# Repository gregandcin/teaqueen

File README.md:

# TeaQueen
An Alice Inspired Split Keyboard

## About the TeaQueen

The TeaQueen is a split, Alice keyboard running QMK firmware, with VIA and Vial compatibility (firmware to be realeased later). Based off of the [Red Queen](https://github.com/dbostian/redqueen) by [Dan Bostian](https://github.com/dbostian). 

V1 of the board, aka the Scuffed Edition, uses Kailh Hotswap sockets and Pro Micro compatitble dev boards, with a focus on [RP2040 Community Edition boards](https://docs.qmk.fm/#/platformdev_rp2040?id=rp2040_ce) such as the Elite-Pi.

## Why?

A PCB made by a factory is easier to assemble than handwiring.

## Want to make modifications?
This PCB uses the [Kiswitch](https://github.com/kiswitch/kiswitch) library as a globally installed pluggin in KiCad 7, so make sure to install that if you want to properly. Otherwise, everything is there for you as local libraries.

## Future Editions
A list of potential TODOs:

- [ ] Regular Solder socket boards
- [ ] An integrated RP2040 MCU
- [ ] A wireless edition

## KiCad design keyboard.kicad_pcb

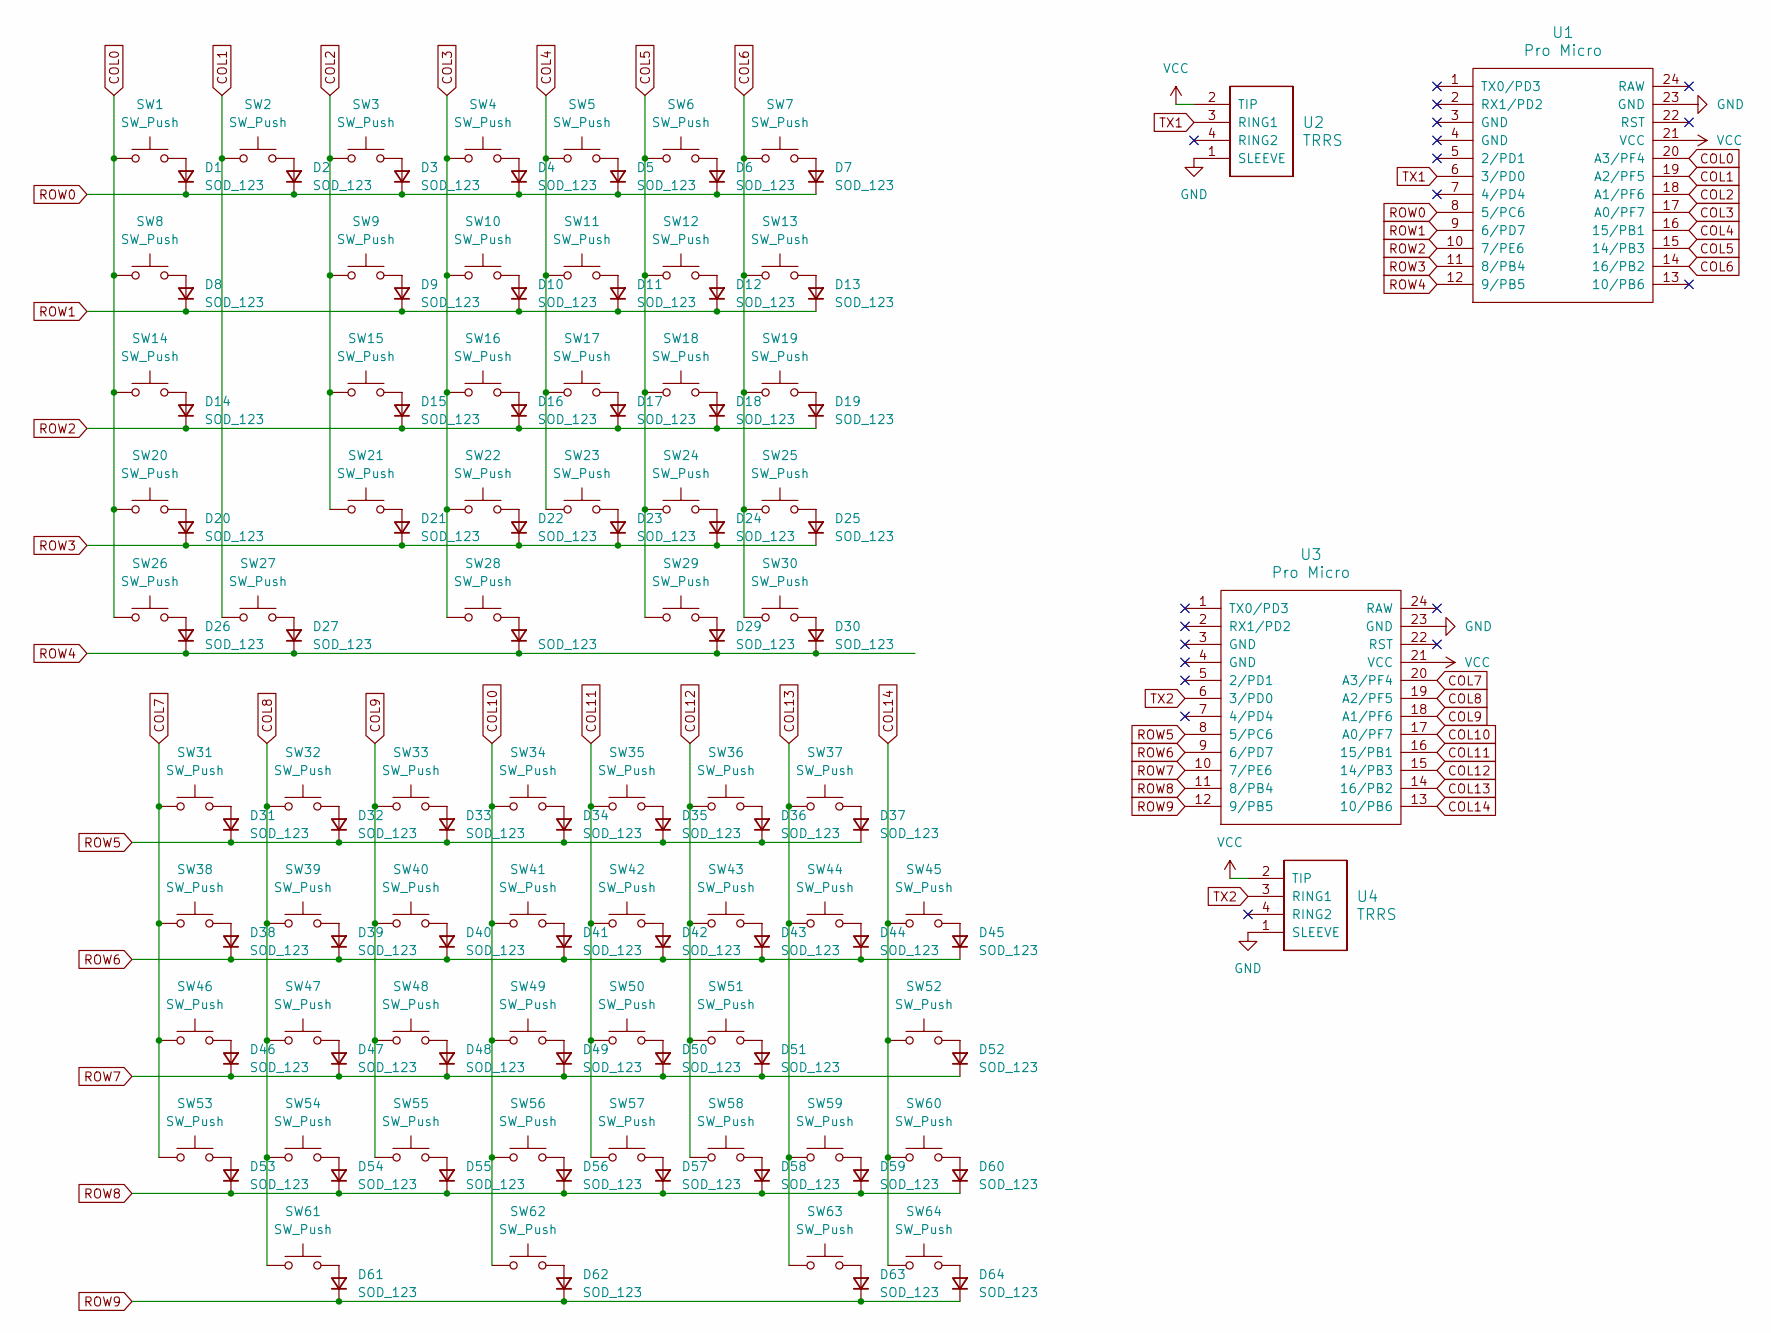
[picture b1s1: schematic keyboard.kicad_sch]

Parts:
D1, D2, D3, D4, D5, D6, D7, D8, D9, D10, D11, D12, D13, D14, D15, D16, D17, D18, D19, D20, D21, D22, D23, D24, D25, D26, D27, D28, D29, D30, D31, D32, D33, D34, D35, D36, D37, D38, D39, D40, D41, D42, D43, D44, D45, D46, D47, D48, D49, D50, D51, D52, D53, D54, D55, D56, D57, D58, D59, D60, D61, D62, D63, D64: SOD_123; D_SOD-123; MPN 1N914BWS; JLCPCB Part # C258181
SW1, SW2, SW3, SW4, SW5, SW6, SW7, SW9, SW10, SW11, SW12, SW13, SW15, SW16, SW17, SW18, SW19, SW21, SW22, SW23, SW24, SW25, SW27, SW30, SW31, SW32, SW33, SW34, SW35, SW36, SW38, SW39, SW40, SW41, SW42, SW43, SW44, SW46, SW47, SW48, SW49, SW50, SW51, SW53, SW54, SW55, SW56, SW57, SW58, SW60, SW63: SW_Push; SW_Hotswap_Kailh_MX_1.00u
SW8, SW26, SW28, SW45, SW62, SW64: SW_Push; SW_Hotswap_Kailh_MX_1.50u
SW14, SW59: SW_Push; SW_Hotswap_Kailh_MX_1.75u
SW20, SW52: SW_Push; SW_Hotswap_Kailh_MX_2.25u
SW29, SW37: SW_Push; SW_Hotswap_Kailh_MX_2.00u
SW61: SW_Push; SW_Hotswap_Kailh_MX_2.75u
U1, U3: Pro Micro; ArduinoProMicro
U2, U4: TRRS; TRRS-PJ-320A; MPN PJ-320A; JLCPCB Part # C2884926

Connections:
COL0: SW1.1, SW8.1, SW14.1, SW20.1, SW26.1, U1.20 (A3/PF4)
COL1: SW2.1, SW27.1, U1.19 (A2/PF5)
COL2: SW3.1, SW9.1, SW15.1, SW21.1, U1.18 (A1/PF6)
COL3: SW4.1, SW10.1, SW16.1, SW22.1, SW28.1, U1.17 (A0/PF7)
COL4: SW5.1, SW11.1, SW17.1, SW23.1, U1.16 (15/PB1)
COL5: SW6.1, SW12.1, SW18.1, SW24.1, SW29.1, U1.15 (14/PB3)
COL6: SW7.1, SW13.1, SW19.1, SW25.1, SW30.1, U1.14 (16/PB2)
COL7: SW31.1, SW38.1, SW46.1, SW53.1, U3.20 (A3/PF4)
COL8: SW32.1, SW39.1, SW47.1, SW54.1, SW61.1, U3.19 (A2/PF5)
COL9: SW33.1, SW40.1, SW48.1, SW55.1, U3.18 (A1/PF6)
COL10: SW34.1, SW41.1, SW49.1, SW56.1, SW62.1, U3.17 (A0/PF7)
COL11: SW35.1, SW42.1, SW50.1, SW57.1, U3.16 (15/PB1)
COL12: SW36.1, SW43.1, SW51.1, SW58.1, U3.15 (14/PB3)
COL13: SW37.1, SW44.1, SW59.1, SW63.1, U3.14 (16/PB2)
COL14: SW45.1, SW52.1, SW60.1, SW64.1, U3.13 (10/PB6)
GND: U1.23 (GND), U2.1 (SLEEVE), U3.23 (GND), U4.1 (SLEEVE)
unnamed: D1.2 (A), SW1.2
unnamed: D2.2 (A), SW2.2
unnamed: D3.2 (A), SW3.2
unnamed: D4.2 (A), SW4.2
unnamed: D5.2 (A), SW5.2
unnamed: D6.2 (A), SW6.2
unnamed: D7.2 (A), SW7.2
unnamed: D8.2 (A), SW8.2
unnamed: D9.2 (A), SW9.2
unnamed: D10.2 (A), SW10.2
unnamed: D11.2 (A), SW11.2
unnamed: D12.2 (A), SW12.2
unnamed: D13.2 (A), SW13.2
unnamed: D14.2 (A), SW14.2
unnamed: D15.2 (A), SW15.2
unnamed: D16.2 (A), SW16.2
unnamed: D17.2 (A), SW17.2
unnamed: D18.2 (A), SW18.2
unnamed: D19.2 (A), SW19.2
unnamed: D20.2 (A), SW20.2
unnamed: D21.2 (A), SW21.2
unnamed: D22.2 (A), SW22.2
unnamed: D23.2 (A), SW23.2
unnamed: D24.2 (A), SW24.2
unnamed: D25.2 (A), SW25.2
unnamed: D26.2 (A), SW26.2
unnamed: D27.2 (A), SW27.2
unnamed: D28.2 (A), SW28.2
unnamed: D29.2 (A), SW29.2
unnamed: D30.2 (A), SW30.2
unnamed: D31.2 (A), SW31.2
unnamed: D32.2 (A), SW32.2
unnamed: D33.2 (A), SW33.2
unnamed: D34.2 (A), SW34.2
unnamed: D35.2 (A), SW35.2
unnamed: D36.2 (A), SW36.2
unnamed: D37.2 (A), SW37.2
unnamed: D38.2 (A), SW38.2
unnamed: D39.2 (A), SW39.2
unnamed: D40.2 (A), SW40.2
unnamed: D41.2 (A), SW41.2
unnamed: D42.2 (A), SW42.2
unnamed: D43.2 (A), SW43.2
unnamed: D44.2 (A), SW44.2
unnamed: D45.2 (A), SW45.2
unnamed: D46.2 (A), SW46.2
unnamed: D47.2 (A), SW47.2
unnamed: D48.2 (A), SW48.2
unnamed: D49.2 (A), SW49.2
unnamed: D50.2 (A), SW50.2
unnamed: D51.2 (A), SW51.2
unnamed: D52.2 (A), SW52.2
unnamed: D53.2 (A), SW53.2
unnamed: D54.2 (A), SW54.2
unnamed: D55.2 (A), SW55.2
unnamed: D56.2 (A), SW56.2
unnamed: D57.2 (A), SW57.2
unnamed: D58.2 (A), SW58.2
unnamed: D59.2 (A), SW59.2
unnamed: D60.2 (A), SW60.2
unnamed: D61.2 (A), SW61.2
unnamed: D62.2 (A), SW62.2
unnamed: D63.2 (A), SW63.2
unnamed: D64.2 (A), SW64.2
ROW0: D1.1 (K), D2.1 (K), D3.1 (K), D4.1 (K), D5.1 (K), D6.1 (K), D7.1 (K), U1.8 (5/PC6)
ROW1: D8.1 (K), D9.1 (K), D10.1 (K), D11.1 (K), D12.1 (K), D13.1 (K), U1.9 (6/PD7)
ROW2: D14.1 (K), D15.1 (K), D16.1 (K), D17.1 (K), D18.1 (K), D19.1 (K), U1.10 (7/PE6)
ROW3: D20.1 (K), D21.1 (K), D22.1 (K), D23.1 (K), D24.1 (K), D25.1 (K), U1.11 (8/PB4)
ROW4: D26.1 (K), D27.1 (K), D28.1 (K), D29.1 (K), D30.1 (K), U1.12 (9/PB5)
ROW5: D31.1 (K), D32.1 (K), D33.1 (K), D34.1 (K), D35.1 (K), D36.1 (K), D37.1 (K), U3.8 (5/PC6)
ROW6: D38.1 (K), D39.1 (K), D40.1 (K), D41.1 (K), D42.1 (K), D43.1 (K), D44.1 (K), D45.1 (K), U3.9 (6/PD7)
ROW7: D46.1 (K), D47.1 (K), D48.1 (K), D49.1 (K), D50.1 (K), D51.1 (K), D52.1 (K), U3.10 (7/PE6)
ROW8: D53.1 (K), D54.1 (K), D55.1 (K), D56.1 (K), D57.1 (K), D58.1 (K), D59.1 (K), D60.1 (K), U3.11 (8/PB4)
ROW9: D61.1 (K), D62.1 (K), D63.1 (K), D64.1 (K), U3.12 (9/PB5)
TX1: U1.6 (3/PD0), U2.3 (RING1)
TX2: U3.6 (3/PD0), U4.3 (RING1)
VCC: U1.21 (VCC), U2.2 (TIP), U3.21 (VCC), U4.2 (TIP)

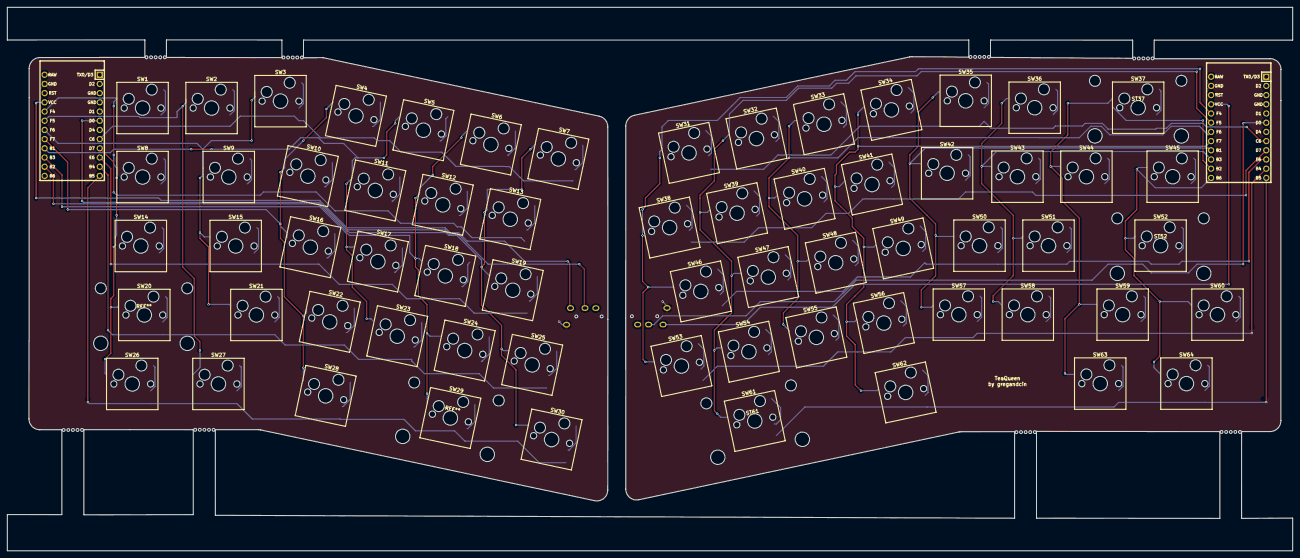
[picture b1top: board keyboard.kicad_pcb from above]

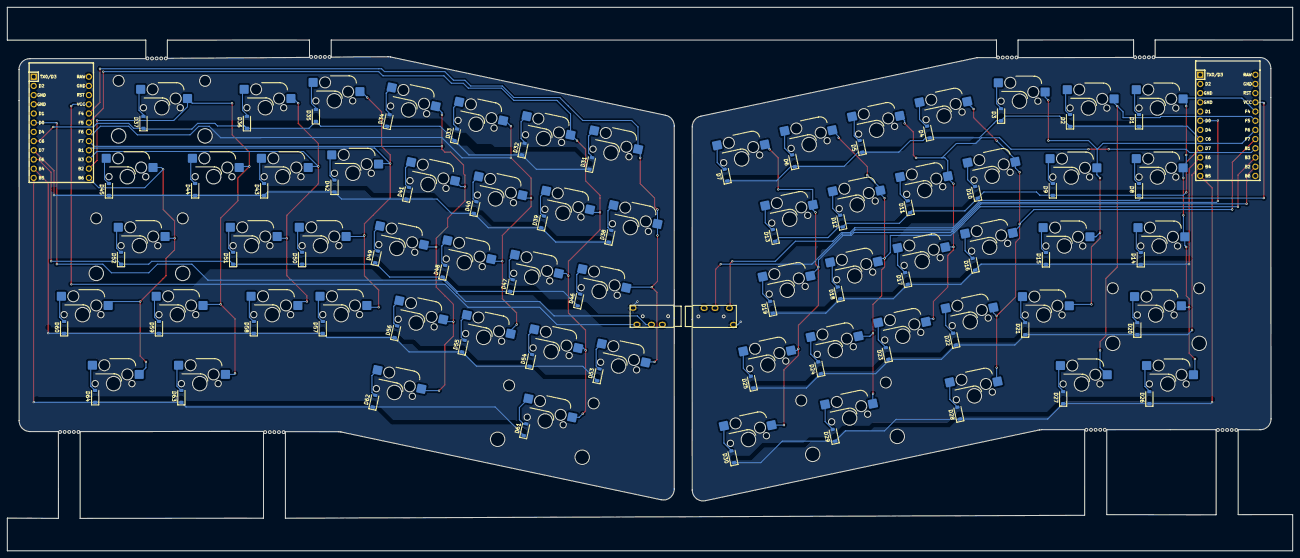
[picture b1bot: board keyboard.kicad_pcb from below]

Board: 2 copper layers, 355.0 x 150.1 mm, 135 parts (68 on the bottom side), 93 nets.

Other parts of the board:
ST37, ST52, ST61: MountingHole; Stabilizer_Cherry_MX_2.00u

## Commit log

2023-10-01 Remove second connection from TRRS and ProMicro, redo traces on PCB to be cleaner
2023-10-04 Redo edge cuts, panelize PCB edge cuts
2023-10-13 Add missing route
2023-10-13 Add LICENSE
2023-10-13 Redo some of the panels
2023-10-13 Redo reouting to reduce number of vias
2023-10-13 Fix mousebite holes going further than pcb edge
2023-10-13 Move TRRS jacks around
2023-10-14 Clean up routes
2023-10-15 Add ground fill
2023-10-15 Redo edge cut corners
2023-10-15 Add JLCPCB part numbers
2023-10-15 Update Diode names
2023-10-17 Change from SOD_323F to SOD_123 footprint for diodes
